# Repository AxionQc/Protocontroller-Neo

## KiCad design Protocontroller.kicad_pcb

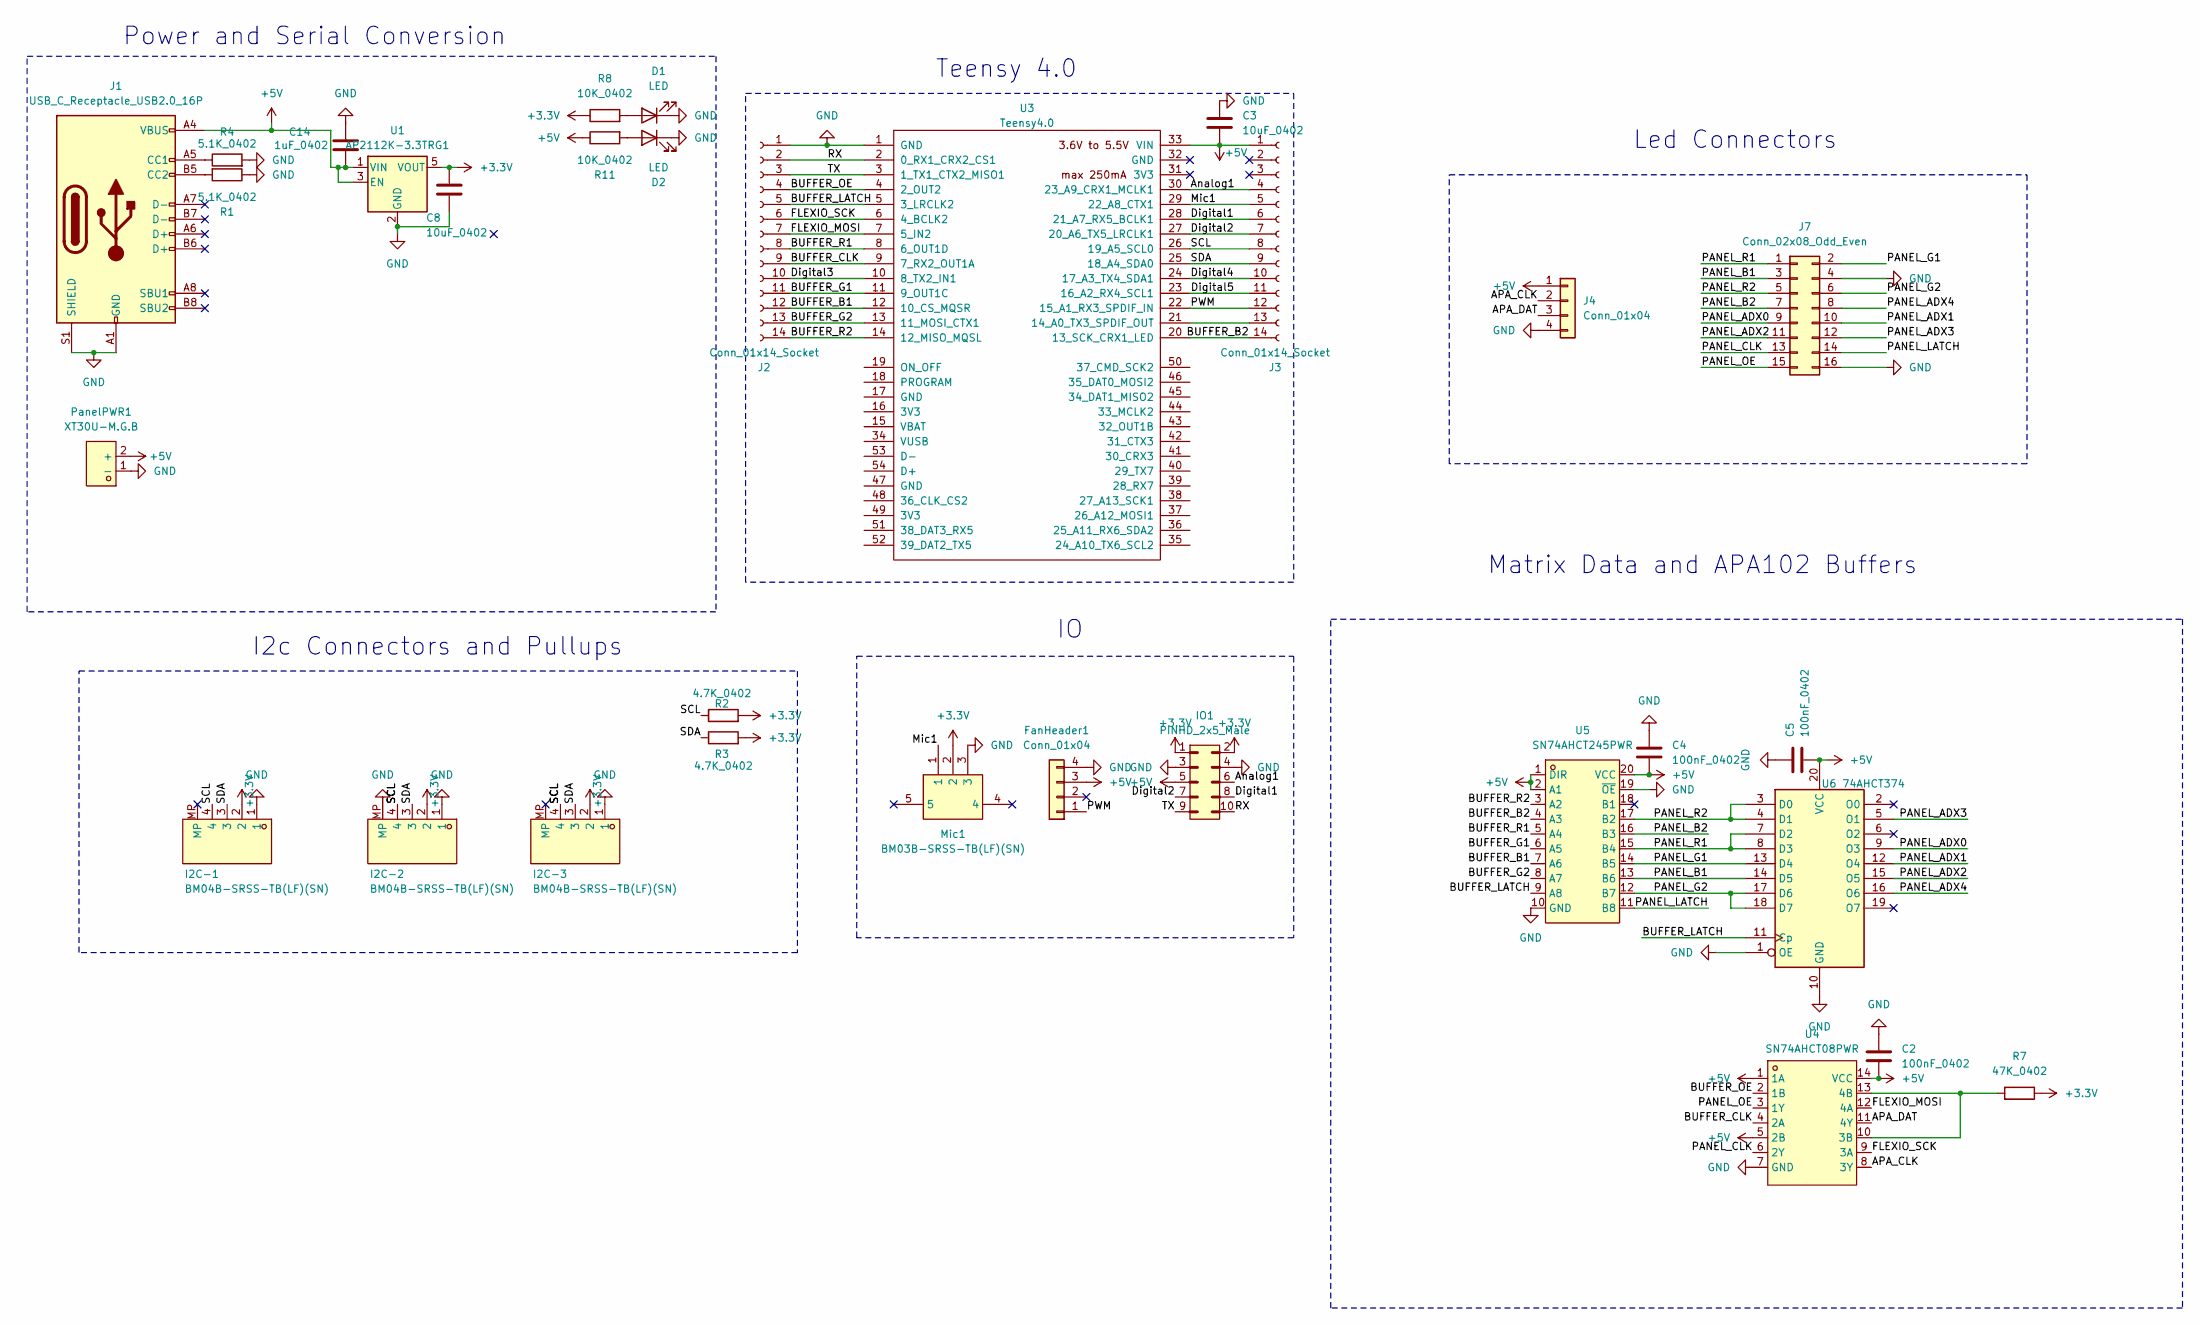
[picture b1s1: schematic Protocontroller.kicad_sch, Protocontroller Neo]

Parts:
C2, C4, C5: 100nF_0402; C_0402_1005Metric; JLC C1525
C3: 10uF_0402; C_0402_1005Metric; LCSC Part C15525
C8: 10uF_0402; C_0402_1005Metric; JLC C15525
C14: 1uF_0402; C_0402_1005Metric; LCSC Part C52923
D1, D2: LED; LED_0603_1608Metric; JLC C7496831
FanHeader1: Conn_01x04; PinHeader_1x04_P2.54mm_Vertical; JLC C2691448
I2C-1, I2C-2, I2C-3: BM04B-SRSS-TB(LF)(SN); CONN-SMD_BM04B-SRSS-TB; LCSC Part C160390
IO1: PINHD_2x5_Male; PinHeader_2x05_P2.54mm_Horizontal; JLC C5383090
J1: USB_C_Receptacle_USB2.0_16P; USB-TH_TYPE-C-16PFS-LCH7.45-IPX8; LCSC Part C3020054
J2, J3: Conn_01x14_Socket; PinSocket_1x14_P2.54mm_Vertical; JLC C2897377
J4: Conn_01x04; JST_SM 1x04 Pad
J7: Conn_02x08_Odd_Even; IDC-Header_2x08_P2.54mm_Horizontal; JLC C7430324
Mic1: BM03B-SRSS-TB(LF)(SN); JST_SH_BM03B-SRSS-TB_1x03-1MP_P1.00mm_Vertical; LCSC Part C160389
PanelPWR1: XT30U-M.G.B; AMASS_XT30U-M_1x02_P5.0mm_Vertical; LCSC Part C19268020
R1, R4: 5.1K_0402; R_0402_1005Metric; LCSC Part C25905
R2, R3: 4.7K_0402; R_0402_1005Metric; LCSC Part C25900
R7: 47K_0402; R_0402_1005Metric; JLC C25792
R8, R11: 10K_0402; R_0402_1005Metric; LCSC Part C25744
U1: AP2112K-3.3TRG1; SOT-23-5
U3: Teensy4.0; Teensy40_SMT
U4: SN74AHCT08PWR; TSSOP-14_L5.0-W4.4-P0.65-LS6.4-BL; LCSC Part C155175
U5: SN74AHCT245PWR; TSSOP-20_L6.5-W4.4-P0.65-LS6.4-BL; LCSC Part C10910
U6: 74AHCT374; SN74AHCT374PWR; JLC C141313

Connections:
+3.3V: C8.1, I2C-1.2, I2C-2.2, I2C-3.2, IO1.1, IO1.2, Mic1.2, R2.2, R3.2, R7.1, R8.1, U1.5 (VOUT)
+5V: C2.2, C3.2, C4.2, C5.2, C14.1, FanHeader1.3, IO1.5, J1.A4 (VBUS), J1.A9 (VBUS), J1.B4 (VBUS), J1.B9 (VBUS), J3.1, J4.1, PanelPWR1.2 (+), R11.1, U1.1 (VIN), U1.3 (EN), U3.33 (VIN), U4.1 (1A), U4.5 (2B), U4.14 (VCC), U5.1 (DIR), U5.2 (A1), U5.20 (VCC), U6.20 (VCC)
/APA_CLK: J4.2, U4.8 (3Y)
/APA_DAT: J4.3, U4.11 (4Y)
/Analog1: IO1.6, J3.4, U3.30 (23_A9_CRX1_MCLK1)
/BUFFER_B1: J2.12, U3.12 (10_CS_MQSR), U5.7 (A6)
/BUFFER_B2: J3.14, U3.20 (13_SCK_CRX1_LED), U5.4 (A3)
/BUFFER_CLK: J2.9, U3.9 (7_RX2_OUT1A), U4.4 (2A)
/BUFFER_G1: J2.11, U3.11 (9_OUT1C), U5.6 (A5)
/BUFFER_G2: J2.13, U3.13 (11_MOSI_CTX1), U5.8 (A7)
/BUFFER_LATCH: J2.5, U3.5 (3_LRCLK2), U5.9 (A8), U6.11 (Cp)
/BUFFER_OE: J2.4, U3.4 (2_OUT2), U4.2 (1B)
/BUFFER_R1: J2.8, U3.8 (6_OUT1D), U5.5 (A4)
/BUFFER_R2: J2.14, U3.14 (12_MISO_MQSL), U5.3 (A2)
/Digital1: IO1.8, J3.6, U3.28 (21_A7_RX5_BCLK1)
/Digital2: IO1.7, J3.7, U3.27 (20_A6_TX5_LRCLK1)
/Digital3: J2.10, U3.10 (8_TX2_IN1)
/Digital4: J3.10, U3.24 (17_A3_TX4_SDA1)
/Digital5: J3.11, U3.23 (16_A2_RX4_SCL1)
/FLEXIO_MOSI: J2.7, U3.7 (5_IN2), U4.12 (4A)
/FLEXIO_SCK: J2.6, U3.6 (4_BCLK2), U4.9 (3A)
/Mic1: J3.5, Mic1.1, U3.29 (22_A8_CTX1)
/PANEL_ADX0: J7.9, U6.9 (O3)
/PANEL_ADX1: J7.10, U6.12 (O4)
/PANEL_ADX2: J7.11, U6.15 (O5)
/PANEL_ADX3: J7.12, U6.5 (O1)
/PANEL_ADX4: J7.8, U6.16 (O6)
/PANEL_B1: J7.3, U5.13 (B6), U6.14 (D5)
/PANEL_B2: J7.7, U5.16 (B3)
/PANEL_CLK: J7.13, U4.6 (2Y)
/PANEL_G1: J7.2, U5.14 (B5), U6.13 (D4)
/PANEL_G2: J7.6, U5.12 (B7), U6.17 (D6), U6.18 (D7)
/PANEL_LATCH: J7.14, U5.11 (B8)
/PANEL_OE: J7.15, U4.3 (1Y)
/PANEL_R1: J7.1, U5.15 (B4), U6.7 (D2), U6.8 (D3)
/PANEL_R2: J7.5, U5.17 (B2), U6.3 (D0), U6.4 (D1)
/PWM: FanHeader1.1, J3.12, U3.22 (15_A1_RX3_SPDIF_IN)
/RX: IO1.10, J2.2, U3.2 (0_RX1_CRX2_CS1)
/SCL: I2C-1.4, I2C-2.4, I2C-3.4, J3.8, R2.1, U3.26 (19_A5_SCL0)
/SDA: I2C-1.3, I2C-2.3, I2C-3.3, J3.9, R3.1, U3.25 (18_A4_SDA0)
/TX: IO1.9, J2.3, U3.3 (1_TX1_CTX2_MISO1)
GND: C2.1, C3.1, C4.1, C5.1, C8.2, C14.2, D1.1 (K), D2.1 (K), FanHeader1.4, I2C-1.1, I2C-2.1, I2C-2.MP, I2C-3.1, I2C-3.MP, IO1.3, IO1.4, J1.A1 (GND), J1.A12 (GND), J1.B1 (GND), J1.B12 (GND), J1.S1 (SHIELD), J2.1, J4.4, J7.4, J7.16, Mic1.3, PanelPWR1.1 (-), R1.1, R4.2, U1.2 (GND), U3.1 (GND), U4.7 (GND), U5.10 (GND), U5.19 (~OE), U6.1 (OE), U6.10 (GND)
unnamed: D1.2 (A), R8.2
unnamed: D2.2 (A), R11.2
unnamed: J1.A5 (CC1), R4.1
unnamed: J1.B5 (CC2), R1.2
unnamed: J3.13, U3.21 (14_A0_TX3_SPDIF_OUT)
unnamed: R7.2, U4.10 (3B), U4.13 (4B)

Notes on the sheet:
Matrix Data and APA102 Buffers
Led Connectors
Teensy 4.0
I2c Connectors and Pullups
Power and Serial Conversion

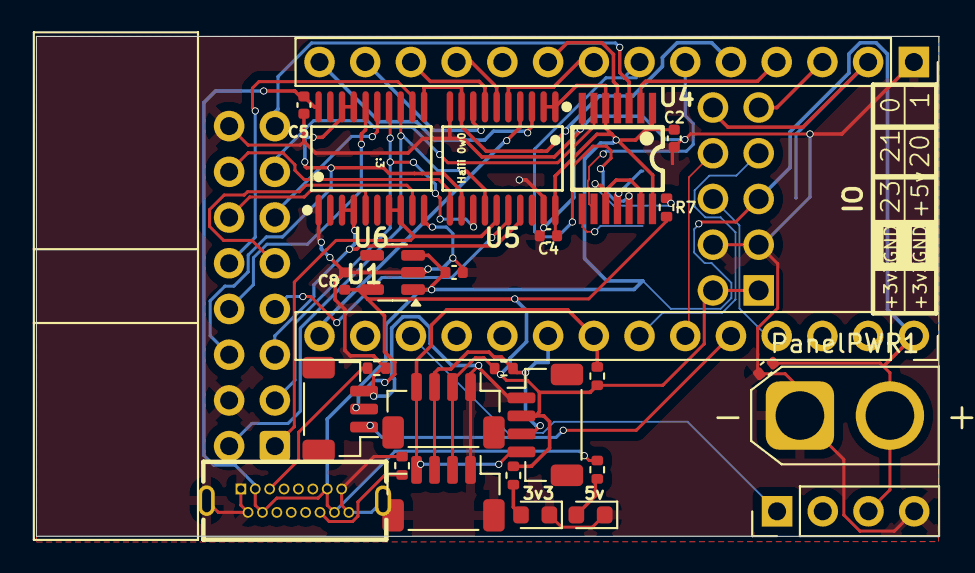
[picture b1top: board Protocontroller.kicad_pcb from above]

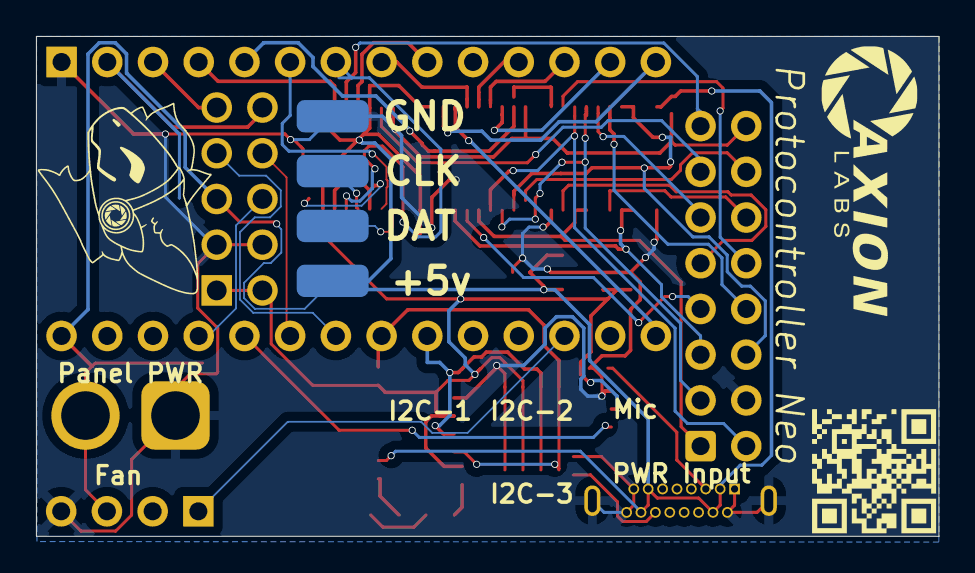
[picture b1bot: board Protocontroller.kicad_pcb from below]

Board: 2 copper layers, 50.1 x 27.8 mm, 33 parts (2 on the bottom side), 44 nets.

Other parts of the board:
AxionLogo: LOGO
Qr: LOGO

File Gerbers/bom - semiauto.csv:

Designator,Footprint,Quantity,Value,LCSC Part #
C14,0402,1,1uF_0402,C52923
"C2, C4, C5",0402,3,100nF_0402,C1525
"C3, C8",0402,2,10uF_0402,C15525
"D1, D2",0603,2,LED,C7496831
"I2C-1, I2C-2, I2C-3",JST_SH_BM04B-SRSS-TB_1x04-1MP_P1.00mm_Vertical,3,BM04B-SRSS-TB(LF)(SN),C160390
J1,USB-TH_TYPE-C-16PFS-LCH7.45-IPX8,1,USB_C_Receptacle_USB2.0_16P,C3020054
MIC1,JST_SH_BM03B-SRSS-TB_1x03-1MP_P1.00mm_Vertical,1,BM03B-SRSS-TB(LF)(SN),C160389
"R1, R4",0402,2,5.1K_0402,C25905
"R11, R8",0402,2,10K_0402,C25744
"R2, R3",0402,2,4.7K_0402,C25900
R7,0402,1,47K_0402,C25792
U1,SOT-23-5,1,AP2112K-3.3TRG1,
U4,TSSOP-14_L5.0-W4.4-P0.65-LS6.4-BL,1,SN74AHCT08PWR,C155175
U5,TSSOP-20_L6.5-W4.4-P0.65-LS6.4-BL,1,SN74AHCT245PWR,C10910
U6,SN74AHCT374PWR,1,74AHCT374,C141313

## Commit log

2025-05-31 Add everything
2025-05-31 Add the CERN-OHL-S Licence
2025-06-01 Fix I2C, Pathing, and improve Silkscreen
2025-06-01 Fix 3v3 Trace
2025-06-01 Add Updated Gerber
2025-06-01 Remove WS35 Support, Adjust Traces, Fix issue with Panel out not actually being connected to anything
2025-06-01 Fix 3v3 Regulator having bad Rotation, Fix issue of Mic and Led's being replaced when updating from schematic.
2025-06-02 Switch Pullups to use 4.7k Resistors for improved speeds, Adjusted capacitors, removed Designators file
2025-06-03 Removed 0201 Resistors for Compatablity with Economic PCBA's, moved JST SH ports so I2C-1 Pins dont phase through teensy headers
2025-06-15 Fix Compat with Economic Again
2025-06-23 Fix Economic Again, fix R1 not being connected, V2 tba
2025-07-10 V2 of the neo released, switched stemma to stemma qt, adjusted io pinout, replaced secondary 74245 with the 7408, swapped apaclk and apadat, switched to 2 layer for cheaper costs, esp32 schematic in,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
2025-10-01 new layout, bunch of empty space
2025-10-01 fix files
2025-10-01 adjusted i2c position and ubc position
